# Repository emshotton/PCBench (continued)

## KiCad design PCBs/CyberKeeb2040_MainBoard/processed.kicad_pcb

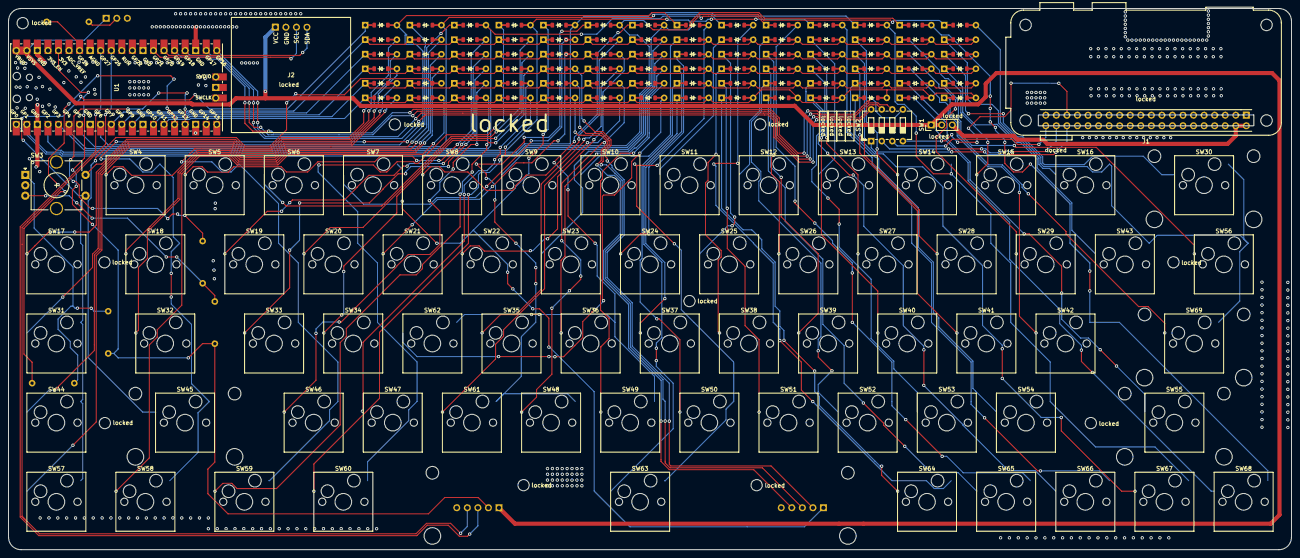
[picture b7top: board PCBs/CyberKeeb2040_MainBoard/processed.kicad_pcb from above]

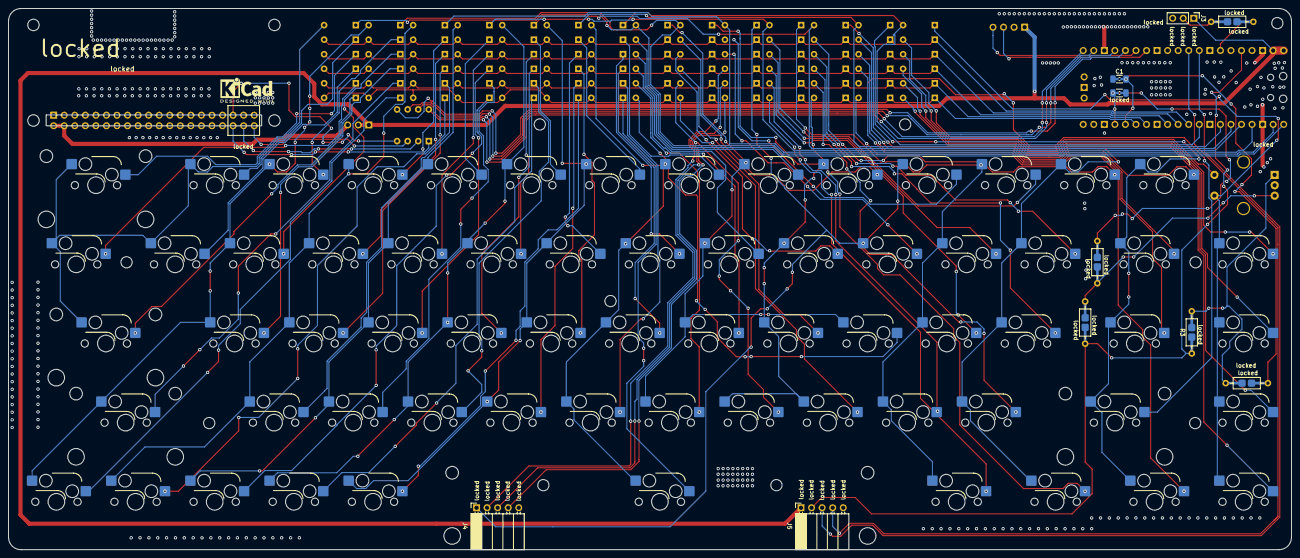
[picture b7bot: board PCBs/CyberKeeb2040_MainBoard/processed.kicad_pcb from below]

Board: 2 copper layers, 308.8 x 130.2 mm, 166 parts (76 on the bottom side), 118 nets.

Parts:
C1: 0.01 μF; C_1206_3216Metric_Pad1.33x1.80mm_HandSolder
D1, D2, D3, D4, D5, D6, D7, D8, D9, D10, D11, D12, D13, D14, D15, D16, D17, D18, D19, D20, D21, D22, D23, D24, D25, D26, D27, D28, D29, D30, D31, D32, D33, D34, D35, D36, D37, D38, D39, D40, D41, D42, D43, D44, D45, D46, D47, D48, D49, D50, D51, D52, D53, D54, D55, D56, D57, D58, D59, D60, D61, D62, D63, D64, D65, D66, D67, D68, D69, D70, D71, D72, D73, D74, D75, D76, D77, D78, D79, D80, D81, D82, D83, D84: D; D_DO-35_SOD27_P7.62mm_Horizontal
J1: Pi_Zero; Raspberry_Pi_Zero_Socketed_THT_MountingHoles_Castellated
J2: JMD0.96C
J3: WS2812; PinHeader_1x03_P2.54mm_Vertical
J4: Extra_Keys; PinSocket_1x05_P2.54mm_Horizontal
J5: JoyStick_Or_I2C1; PinSocket_1x05_P2.54mm_Horizontal
R1: 330; R_Axial_DIN0207_L6.3mm_D2.5mm_P10.16mm_Horizontal_0603
R2, R3, R4, R5: 10k; R_Axial_DIN0207_L6.3mm_D2.5mm_P10.16mm_Horizontal_0402
SW1: PiPowerSwitch; PinHeader_1x03_P2.54mm_Vertical
SW2: SPI_SW; SW_DIP_SPSTx04_Slide_6.7x11.72mm_W7.62mm_P2.54mm_LowProfile
SW3: RotaryEncoder_Switch; RotaryEncoder_Alps_EC11E-Switch_Vertical_H20mm_CircularMoun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
SW4: SW_`; SW_Hotswap_Kailh_MX_1.00u
SW5: SW_1; SW_Hotswap_Kailh_MX_1.00u
SW6: SW_2; SW_Hotswap_Kailh_MX_1.00u
SW7: SW_3; SW_Hotswap_Kailh_MX_1.00u
SW8: SW_4; SW_Hotswap_Kailh_MX_1.00u
SW9: SW_5; SW_Hotswap_Kailh_MX_1.00u
SW10: SW_6; SW_Hotswap_Kailh_MX_1.00u
SW11: SW_7; SW_Hotswap_Kailh_MX_1.00u
SW12: SW_8; SW_Hotswap_Kailh_MX_1.00u
SW13: SW_9; SW_Hotswap_Kailh_MX_1.00u
SW14: SW_0; SW_Hotswap_Kailh_MX_1.00u
SW15: SW_-; SW_Hotswap_Kailh_MX_1.00u
SW16: SW_+; SW_Hotswap_Kailh_MX_1.00u
SW17: SW_esc; SW_Hotswap_Kailh_MX_1.00u
SW18: SW_tab; SW_Hotswap_Kailh_MX_1.50u
SW19: SW_q; SW_Hotswap_Kailh_MX_1.00u
SW20: SW_w; SW_Hotswap_Kailh_MX_1.00u
SW21: SW_e; SW_Hotswap_Kailh_MX_1.00u
SW22: SW_r; SW_Hotswap_Kailh_MX_1.00u
SW23: SW_t; SW_Hotswap_Kailh_MX_1.00u
SW24: SW_y; SW_Hotswap_Kailh_MX_1.00u
SW25: SW_u; SW_Hotswap_Kailh_MX_1.00u
SW26: SW_i; SW_Hotswap_Kailh_MX_1.00u
SW27: SW_o; SW_Hotswap_Kailh_MX_1.00u
SW28: SW_p; SW_Hotswap_Kailh_MX_1.00u
SW29: SW_[; SW_Hotswap_Kailh_MX_1.00u
SW30: SW_back; SW_Hotswap_Kailh_MX_2.00u
SW31: SW_del; SW_Hotswap_Kailh_MX_1.00u
SW32: SW_caps; SW_Hotswap_Kailh_MX_1.75u
SW33: SW_a; SW_Hotswap_Kailh_MX_1.00u
SW34: SW_s; SW_Hotswap_Kailh_MX_1.00u
SW35: SW_f; SW_Hotswap_Kailh_MX_1.00u
SW36: SW_g; SW_Hotswap_Kailh_MX_1.00u
SW37: SW_h; SW_Hotswap_Kailh_MX_1.00u
SW38: SW_j; SW_Hotswap_Kailh_MX_1.00u
SW39: SW_k; SW_Hotswap_Kailh_MX_1.00u
SW40: SW_l; SW_Hotswap_Kailh_MX_1.00u
SW41: SW_;; SW_Hotswap_Kailh_MX_1.00u
SW42: SW_'; SW_Hotswap_Kailh_MX_1.00u
SW43: SW_]; SW_Hotswap_Kailh_MX_1.00u
SW44: SW_ins; SW_Hotswap_Kailh_MX_1.00u
SW45: SW_shift; SW_Hotswap_Kailh_MX_2.25u
SW46: SW_z; SW_Hotswap_Kailh_MX_1.00u
SW47: SW_x; SW_Hotswap_Kailh_MX_1.00u
SW48: SW_v; SW_Hotswap_Kailh_MX_1.00u
SW49: SW_b; SW_Hotswap_Kailh_MX_1.00u
SW50: SW_n; SW_Hotswap_Kailh_MX_1.00u
SW51: SW_m; SW_Hotswap_Kailh_MX_1.00u
SW52: SW_,; SW_Hotswap_Kailh_MX_1.00u
SW53: SW_.; SW_Hotswap_Kailh_MX_1.00u
SW54: SW_/; SW_Hotswap_Kailh_MX_1.00u
SW55: SW_r_shift; SW_Hotswap_Kailh_MX_2.75u
SW56: SW_bkslash; SW_Hotswap_Kailh_MX_1.50u
SW57: SW_fn1; SW_Hotswap_Kailh_MX_1.00u
SW58: SW_ctrl; SW_Hotswap_Kailh_MX_1.25u
SW59: SW_super; SW_Hotswap_Kailh_MX_1.25u
SW60: SW_alt; SW_Hotswap_Kailh_MX_1.25u
SW61: SW_c; SW_Hotswap_Kailh_MX_1.00u
SW62: SW_d; SW_Hotswap_Kailh_MX_1.00u
SW63: SW_space; SW_Hotswap_Kailh_MX_6.25u
SW64: SW_fn2; SW_Hotswap_Kailh_MX_1.00u
SW65: SW_left; SW_Hotswap_Kailh_MX_1.00u
SW66: SW_down; SW_Hotswap_Kailh_MX_1.00u
SW67: SW_up; SW_Hotswap_Kailh_MX_1.00u
SW68: SW_right; SW_Hotswap_Kailh_MX_1.00u
SW69: SW_enter; SW_Hotswap_Kailh_MX_2.25u
U1: Pico; RPi_Pico_SMD_TH
locked: 0.01 μF; C_1206_3216Metric_Pad1.33x1.80mm_HandSolder

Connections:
+3V3: J5.2, R3.2, R4.1, U1.36 (3V3)
+5V: J2.1, J3.1, J5.1, SW1.1 (A), SW1.2 (B), U1.39 (VSYS), U1.40 (VBUS)
/Pi_VCC: J1.2, J1.4, SW1.3 (C)
ANG1: J5.3, U1.32 (GPIO27_ADC1)
ANG2: J5.4, U1.31 (GPIO26_ADC0)
C0: D1.2 (A), D8.1 (K), U1.9 (GPIO6)
C1: D2.2 (A), D9.1 (K), U1.7 (GPIO5)
C2: D3.2 (A), D10.1 (K), U1.6 (GPIO4)
C3: D4.2 (A), D11.1 (K), U1.5 (GPIO3)
C4: D5.2 (A), D12.1 (K), U1.4 (GPIO2)
C5: D6.2 (A), D13.1 (K), U1.2 (GPIO1)
C6: D7.2 (A), D14.1 (K), U1.1 (GPIO0)
Enc1: C1.2, R2.1, U1.16 (GPIO12)
Enc2: R5.2, U1.17 (GPIO13), locked.1
Encoder_SW_1: D15.2 (A), SW3.S2
Encoder_SW_2: D1.1 (K), SW3.S1, SW17.2 (B), SW31.2 (B), SW44.2 (B), SW57.2 (B)
Extra1: D47.2 (A), J4.2
Extra2: D61.2 (A), J4.3
Extra3: D75.2 (A), J4.4
ExtraSource: D5.1 (K), J4.1, SW7.2 (B), SW21.2 (B)
GND: C1.1, J1.6, J1.9, J1.14, J1.20, J1.25, J1.30, J1.34, J2.2, J3.3, J4.5, J5.5, SW3.C, U1.3 (GND), U1.8 (GND), U1.13 (GND), U1.18 (GND), U1.23 (GND), U1.28 (GND), U1.38 (GND), locked.2
I2C0_SCL: J2.3, U1.27 (GPIO21)
I2C0_SDA: J2.4, U1.26 (GPIO20)
LED: R1.1, U1.34 (GPIO28_ADC2)
unnamed: D2.1 (K), SW4.2 (B), SW18.2 (B), SW32.2 (B), SW45.2 (B), SW58.2 (B)
unnamed: D3.1 (K), SW5.2 (B), SW19.2 (B), SW33.2 (B), SW46.2 (B), SW59.2 (B)
unnamed: D4.1 (K), SW6.2 (B), SW20.2 (B), SW34.2 (B), SW47.2 (B), SW60.2 (B)
unnamed: D6.1 (K), SW8.2 (B), SW22.2 (B), SW35.2 (B), SW48.2 (B), SW61.2 (B)
unnamed: D7.1 (K), SW9.2 (B), SW23.2 (B), SW36.2 (B), SW49.2 (B), SW62.2 (B)
unnamed: D8.2 (A), SW10.2 (B), SW24.2 (B), SW37.2 (B), SW50.2 (B), SW63.2 (B)
unnamed: D9.2 (A), SW11.2 (B), SW25.2 (B), SW38.2 (B), SW51.2 (B), SW64.2 (B)
unnamed: D10.2 (A), SW12.2 (B), SW26.2 (B), SW39.2 (B), SW52.2 (B), SW65.2 (B)
unnamed: D11.2 (A), SW13.2 (B), SW27.2 (B), SW40.2 (B), SW53.2 (B), SW66.2 (B)
unnamed: D12.2 (A), SW14.2 (B), SW28.2 (B), SW41.2 (B), SW54.2 (B), SW67.2 (B)
unnamed: D13.2 (A), SW15.2 (B), SW29.2 (B), SW42.2 (B), SW55.2 (B), SW68.2 (B)
unnamed: D14.2 (A), SW16.2 (B), SW30.2 (B), SW43.2 (B), SW56.2 (B), SW69.2 (B)
unnamed: D16.2 (A), SW4.1 (A)
unnamed: D17.2 (A), SW5.1 (A)
unnamed: D18.2 (A), SW6.1 (A)
unnamed: D19.2 (A), SW7.1 (A)
unnamed: D20.2 (A), SW8.1 (A)
unnamed: D21.2 (A), SW9.1 (A)
unnamed: D22.1 (K), SW10.1 (A)
unnamed: D23.1 (K), SW11.1 (A)
unnamed: D24.1 (K), SW12.1 (A)
unnamed: D25.1 (K), SW13.1 (A)
unnamed: D26.1 (K), SW14.1 (A)
unnamed: D27.1 (K), SW15.1 (A)
unnamed: D28.1 (K), SW16.1 (A)
unnamed: D29.2 (A), SW17.1 (A)
unnamed: D30.2 (A), SW18.1 (A)
unnamed: D31.2 (A), SW19.1 (A)
unnamed: D32.2 (A), SW20.1 (A)
unnamed: D33.2 (A), SW21.1 (A)
unnamed: D34.2 (A), SW22.1 (A)
unnamed: D35.2 (A), SW23.1 (A)
unnamed: D36.1 (K), SW24.1 (A)
unnamed: D37.1 (K), SW25.1 (A)
unnamed: D38.1 (K), SW26.1 (A)
unnamed: D39.1 (K), SW27.1 (A)
unnamed: D40.1 (K), SW28.1 (A)
unnamed: D41.1 (K), SW29.1 (A)
unnamed: D42.1 (K), SW30.1 (A)
unnamed: D43.2 (A), SW31.1 (A)
unnamed: D44.2 (A), SW32.1 (A)
unnamed: D45.2 (A), SW33.1 (A)
unnamed: D46.2 (A), SW34.1 (A)
unnamed: D48.2 (A), SW35.1 (A)
unnamed: D49.2 (A), SW36.1 (A)
unnamed: D50.1 (K), SW37.1 (A)
unnamed: D51.1 (K), SW38.1 (A)
unnamed: D52.1 (K), SW39.1 (A)
unnamed: D53.1 (K), SW40.1 (A)
unnamed: D54.1 (K), SW41.1 (A)
unnamed: D55.1 (K), SW42.1 (A)
unnamed: D56.1 (K), SW43.1 (A)
unnamed: D57.2 (A), SW44.1 (A)
unnamed: D58.2 (A), SW45.1 (A)
unnamed: D59.2 (A), SW46.1 (A)
unnamed: D60.2 (A), SW47.1 (A)
unnamed: D62.2 (A), SW48.1 (A)
unnamed: D63.2 (A), SW49.1 (A)
unnamed: D64.1 (K), SW50.1 (A)
unnamed: D65.1 (K), SW51.1 (A)
unnamed: D66.1 (K), SW52.1 (A)
unnamed: D67.1 (K), SW53.1 (A)
unnamed: D68.1 (K), SW54.1 (A)
unnamed: D69.1 (K), SW55.1 (A)
unnamed: D70.1 (K), SW56.1 (A)
unnamed: D71.2 (A), SW57.1 (A)
unnamed: D72.2 (A), SW58.1 (A)
unnamed: D73.2 (A), SW59.1 (A)
unnamed: D74.2 (A), SW60.1 (A)
unnamed: D76.2 (A), SW61.1 (A)
unnamed: D77.2 (A), SW62.1 (A)
unnamed: D78.1 (K), SW63.1 (A)
unnamed: D79.1 (K), SW64.1 (A)
unnamed: D80.1 (K), SW65.1 (A)
unnamed: D81.1 (K), SW66.1 (A)
unnamed: D82.1 (K), SW67.1 (A)
unnamed: D83.1 (K), SW68.1 (A)
unnamed: D84.1 (K), SW69.1 (A)
unnamed: J3.2, R1.2
unnamed: R2.2, R3.1, SW3.A
unnamed: R4.2, R5.1, SW3.B
PI_SPI_CS: J1.36, SW2.1
PI_SPI_MISO: J1.35, SW2.4
PI_SPI_MOSI: J1.38, SW2.2
PI_SPI_SCK: J1.40, SW2.3
R0: D15.1 (K), D16.1 (K), D17.1 (K), D18.1 (K), D19.1 (K), D20.1 (K), D21.1 (K), D22.2 (A), D23.2 (A), D24.2 (A), D25.2 (A), D26.2 (A), D27.2 (A), D28.2 (A), U1.10 (GPIO7)
R1: D29.1 (K), D30.1 (K), D31.1 (K), D32.1 (K), D33.1 (K), D34.1 (K), D35.1 (K), D36.2 (A), D37.2 (A), D38.2 (A), D39.2 (A), D40.2 (A), D41.2 (A), D42.2 (A), U1.11 (GPIO8)
R2: D43.1 (K), D44.1 (K), D45.1 (K), D46.1 (K), D47.1 (K), D48.1 (K), D49.1 (K), D50.2 (A), D51.2 (A), D52.2 (A), D53.2 (A), D54.2 (A), D55.2 (A), D56.2 (A), U1.12 (GPIO9)
R3: D57.1 (K), D58.1 (K), D59.1 (K), D60.1 (K), D61.1 (K), D62.1 (K), D63.1 (K), D64.2 (A), D65.2 (A), D66.2 (A), D67.2 (A), D68.2 (A), D69.2 (A), D70.2 (A), U1.14 (GPIO10)
R4: D71.1 (K), D72.1 (K), D73.1 (K), D74.1 (K), D75.1 (K), D76.1 (K), D77.1 (K), D78.2 (A), D79.2 (A), D80.2 (A), D81.2 (A), D82.2 (A), D83.2 (A), D84.2 (A), U1.15 (GPIO11)
SPI_CS: SW2.8, U1.22 (GPIO17)
SPI_MISO: SW2.5, U1.25 (GPIO19)
SPI_MOSI: SW2.7, U1.21 (GPIO16)
SPI_SCK: SW2.6, U1.24 (GPIO18)
